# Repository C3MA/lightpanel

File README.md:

# moved to https://www.ccc-mannheim.de/wiki/Lightpanel

# lightpanel v1.0

###Import application note
Do not chain Multiple boards while powering only via USB!

The Voltage converters will reverse feed the second board, and in the process kill most of the LED's on the first board!

ESP32C3 notice:
If flashing while connected to the board, the ESP might damage it's

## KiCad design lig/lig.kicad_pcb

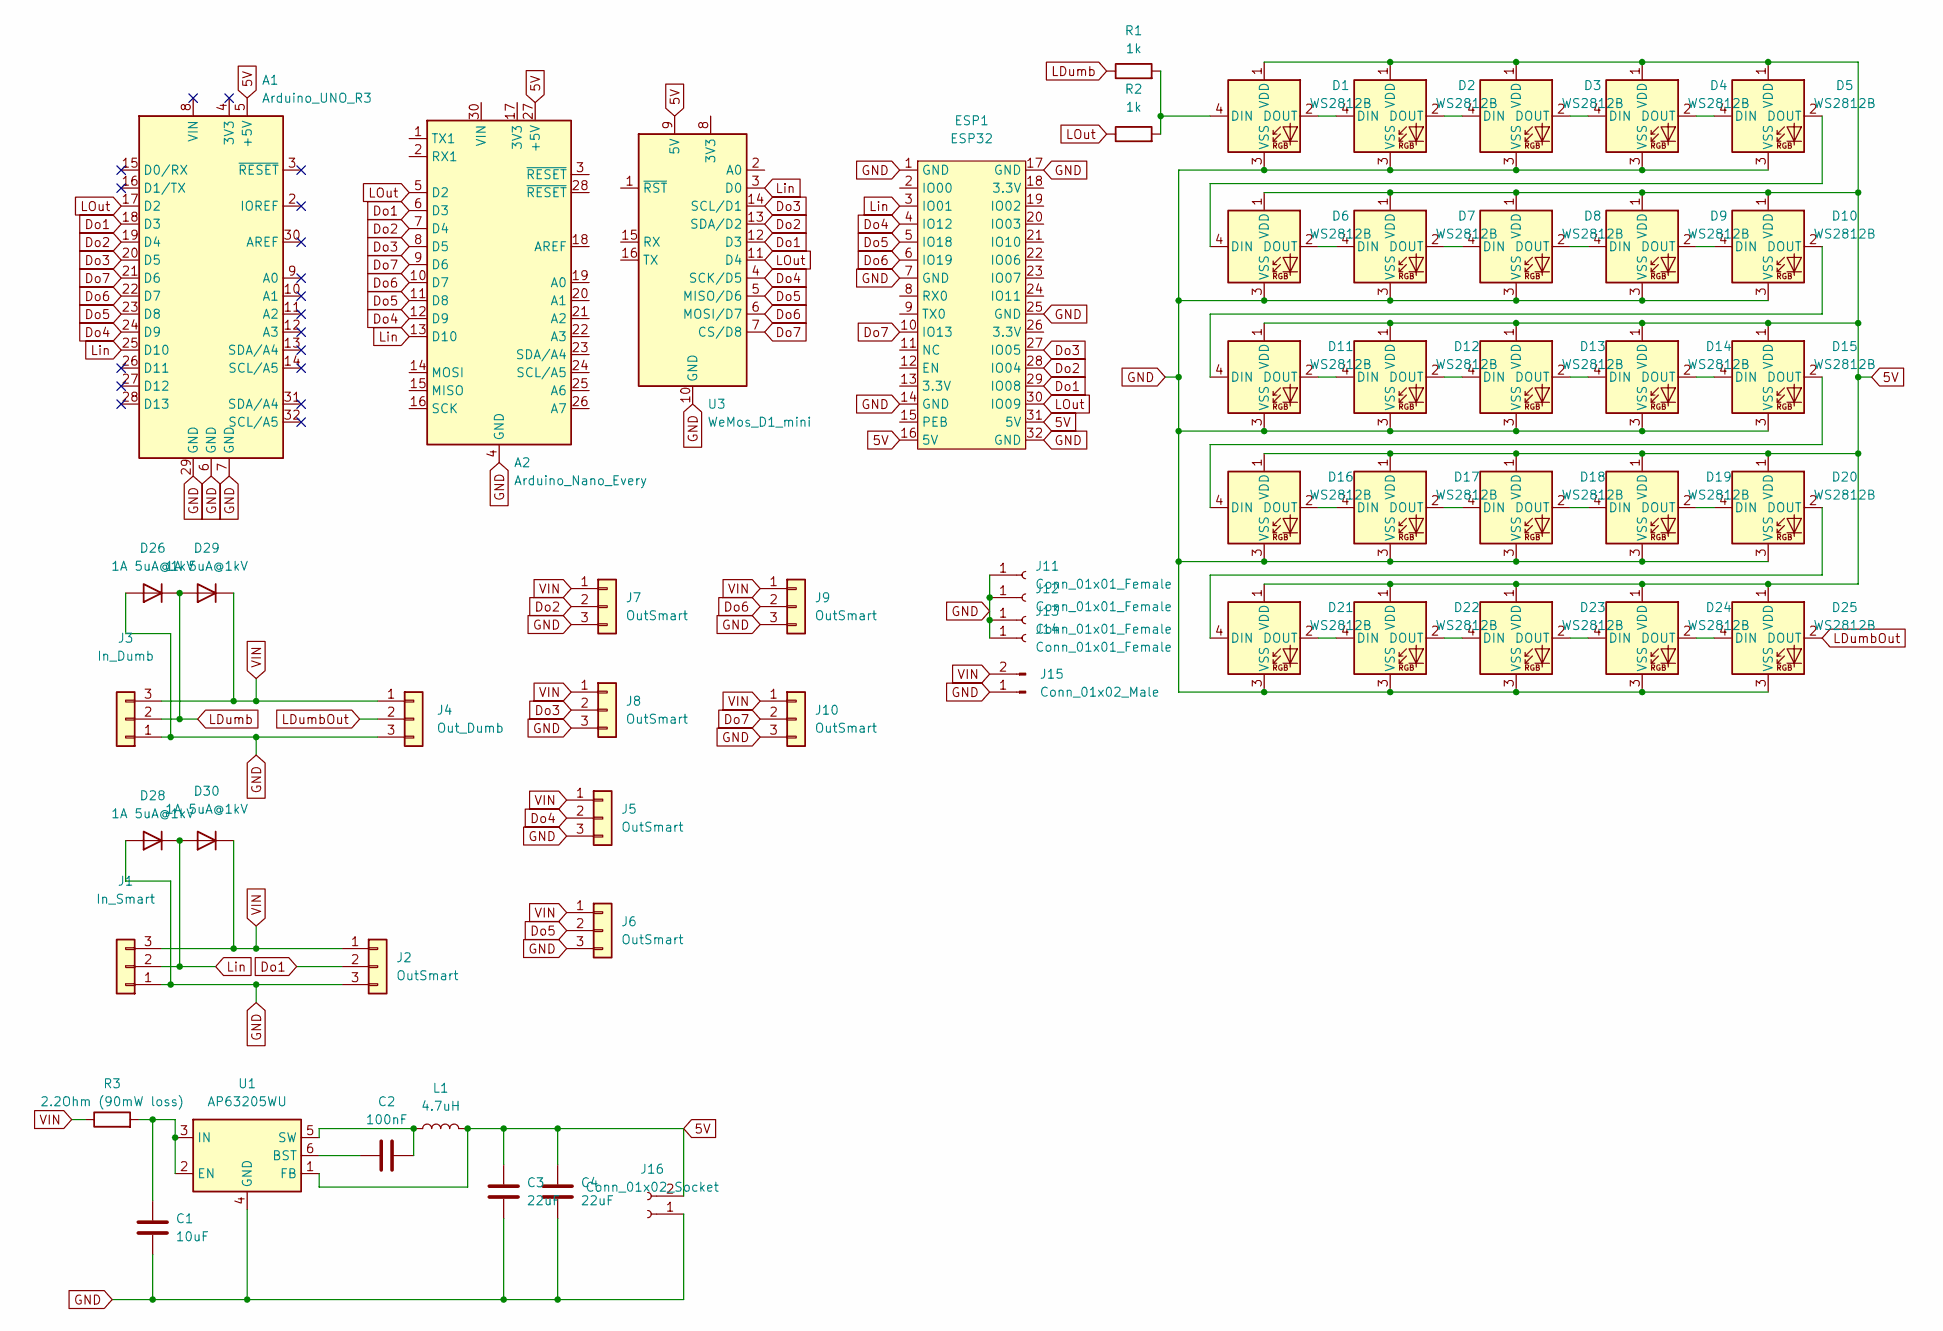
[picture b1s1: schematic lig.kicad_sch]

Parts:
A1: Arduino_UNO_R3
A2: Arduino_Nano_Every; Arduino_Nano
C1: 10uF; C_1206_3216Metric; LCSC C13585
C2: 100nF; C_0603_1608Metric; LCSC C14663
C3, C4: 22uF; C_1206_3216Metric; LCSC C15008
D1, D2, D3, D4, D5, D6, D7, D8, D9, D10, D11, D12, D13, D14, D15, D16, D17, D18, D19, D20, D21, D22, D23, D24, D25: WS2812B; LED_WS2812B_PLCC4_5.0x5.0mm_P3.2mm; LCSC C2843785
D26, D28, D29, D30: 1A 5uA@1kV; D_SOD-123F; LCSC C64898
ESP1: ESP32; Luatos
J1: In_Smart; JST_PH_B3B-PH-SM4-TB_1x03-1MP_P2.00mm_Vertical
J2, J5, J6, J7, J8, J9, J10: OutSmart; JST_PH_B3B-PH-SM4-TB_1x03-1MP_P2.00mm_Vertical
J3: In_Dumb; JST_PH_B3B-PH-SM4-TB_1x03-1MP_P2.00mm_Vertical; LCSC C2688785
J4: Out_Dumb; JST_PH_B3B-PH-SM4-TB_1x03-1MP_P2.00mm_Vertical; LCSC C2688785
J11, J12, J13, J14: Conn_01x01_Female; Solder_Screw_Mount
J15: Conn_01x02_Male; AMASS_XT60-M_1x02_P7.20mm_Vertical
J16: Conn_01x02_Socket; PinHeader_1x02_P2.54mm_Vertical
L1: 4.7uH; L_1210_3225Metric; LCSC C90319
R1, R2: 1k; R_0603_1608Metric; LCSC C21190
R3: 2.2Ohm (90mW loss); R_0805_2012Metric; LCSC C17513
U1: AP63205WU; TSOT-23-6; LCSC C2071056
U3: WeMos_D1_mini; WEMOS_D1_mini_light

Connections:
5V: A1.5 (+5V), A2.27 (+5V), C3.1, C4.1, D1.1 (VDD), D2.1 (VDD), D3.1 (VDD), D4.1 (VDD), D5.1 (VDD), D6.1 (VDD), D7.1 (VDD), D8.1 (VDD), D9.1 (VDD), D10.1 (VDD), D11.1 (VDD), D12.1 (VDD), D13.1 (VDD), D14.1 (VDD), D15.1 (VDD), D16.1 (VDD), D17.1 (VDD), D18.1 (VDD), D19.1 (VDD), D20.1 (VDD), D21.1 (VDD), D22.1 (VDD), D23.1 (VDD), D24.1 (VDD), D25.1 (VDD), ESP1.16 (5V), ESP1.31 (5V), J16.2, L1.2, U1.1 (FB), U3.9 (5V)
Do1: A1.18 (D3), A2.6 (D3), ESP1.29 (IO08), J2.2, U3.12 (D3)
Do2: A1.19 (D4), A2.7 (D4), ESP1.28 (IO04), J7.2, U3.13 (SDA/D2)
Do3: A1.20 (D5), A2.8 (D5), ESP1.27 (IO05), J8.2, U3.14 (SCL/D1)
Do4: A1.24 (D9), A2.12 (D9), ESP1.4 (IO12), J5.2, U3.4 (SCK/D5)
Do5: A1.23 (D8), A2.11 (D8), ESP1.5 (IO18), J6.2, U3.5 (MISO/D6)
Do6: A1.22 (D7), A2.10 (D7), ESP1.6 (IO19), J9.2, U3.6 (MOSI/D7)
Do7: A1.21 (D6), A2.9 (D6), ESP1.10 (IO13), J10.2, U3.7 (CS/D8)
GND: A1.6 (GND), A1.7 (GND), A1.29 (GND), A2.4 (GND), A2.29 (GND), C1.2, C3.2, C4.2, D1.3 (VSS), D2.3 (VSS), D3.3 (VSS), D4.3 (VSS), D5.3 (VSS), D6.3 (VSS), D7.3 (VSS), D8.3 (VSS), D9.3 (VSS), D10.3 (VSS), D11.3 (VSS), D12.3 (VSS), D13.3 (VSS), D14.3 (VSS), D15.3 (VSS), D16.3 (VSS), D17.3 (VSS), D18.3 (VSS), D19.3 (VSS), D20.3 (VSS), D21.3 (VSS), D22.3 (VSS), D23.3 (VSS), D24.3 (VSS), D25.3 (VSS), D26.2 (A), D28.2 (A), ESP1.1 (GND), ESP1.7 (GND), ESP1.14 (GND), ESP1.17 (GND), ESP1.25 (GND), ESP1.32 (GND), J1.1, J2.3, J3.1, J4.3, J5.3, J6.3, J7.3, J8.3, J9.3, J10.3, J11.1, J12.1, J13.1, J14.1, J15.1, J16.1, U1.4 (GND), U3.10 (GND)
LDumb: D26.1 (K), D29.2 (A), J3.2, R1.1
LDumbOut: D25.2 (DOUT), J4.2
LOut: A1.17 (D2), A2.5 (D2), ESP1.30 (IO09), R2.1, U3.11 (D4)
Lin: A1.25 (D10), A2.13 (D10), D28.1 (K), D30.2 (A), ESP1.3 (IO01), J1.2, U3.3 (D0)
unnamed: D1.4 (DIN), R1.2, R2.2
unnamed: D1.2 (DOUT), D2.4 (DIN)
unnamed: D2.2 (DOUT), D3.4 (DIN)
unnamed: D3.2 (DOUT), D4.4 (DIN)
unnamed: D4.2 (DOUT), D5.4 (DIN)
unnamed: D5.2 (DOUT), D6.4 (DIN)
unnamed: D6.2 (DOUT), D7.4 (DIN)
unnamed: D7.2 (DOUT), D8.4 (DIN)
unnamed: D8.2 (DOUT), D9.4 (DIN)
unnamed: D9.2 (DOUT), D10.4 (DIN)
unnamed: D10.2 (DOUT), D11.4 (DIN)
unnamed: D11.2 (DOUT), D12.4 (DIN)
unnamed: D12.2 (DOUT), D13.4 (DIN)
unnamed: D13.2 (DOUT), D14.4 (DIN)
unnamed: D14.2 (DOUT), D15.4 (DIN)
unnamed: D15.2 (DOUT), D16.4 (DIN)
unnamed: D16.2 (DOUT), D17.4 (DIN)
unnamed: D17.2 (DOUT), D18.4 (DIN)
unnamed: D18.2 (DOUT), D19.4 (DIN)
unnamed: D19.2 (DOUT), D20.4 (DIN)
unnamed: D20.2 (DOUT), D21.4 (DIN)
unnamed: D21.2 (DOUT), D22.4 (DIN)
unnamed: D22.2 (DOUT), D23.4 (DIN)
unnamed: D23.2 (DOUT), D24.4 (DIN)
unnamed: D24.2 (DOUT), D25.4 (DIN)
unnamed: C2.1, U1.6 (BST)
unnamed: C1.1, R3.2, U1.2 (EN), U1.3 (IN)
unnamed: C2.2, L1.1, U1.5 (SW)
VIN: D29.1 (K), D30.1 (K), J1.3, J2.1, J3.3, J4.1, J5.1, J6.1, J7.1, J8.1, J9.1, J10.1, J15.2, R3.1

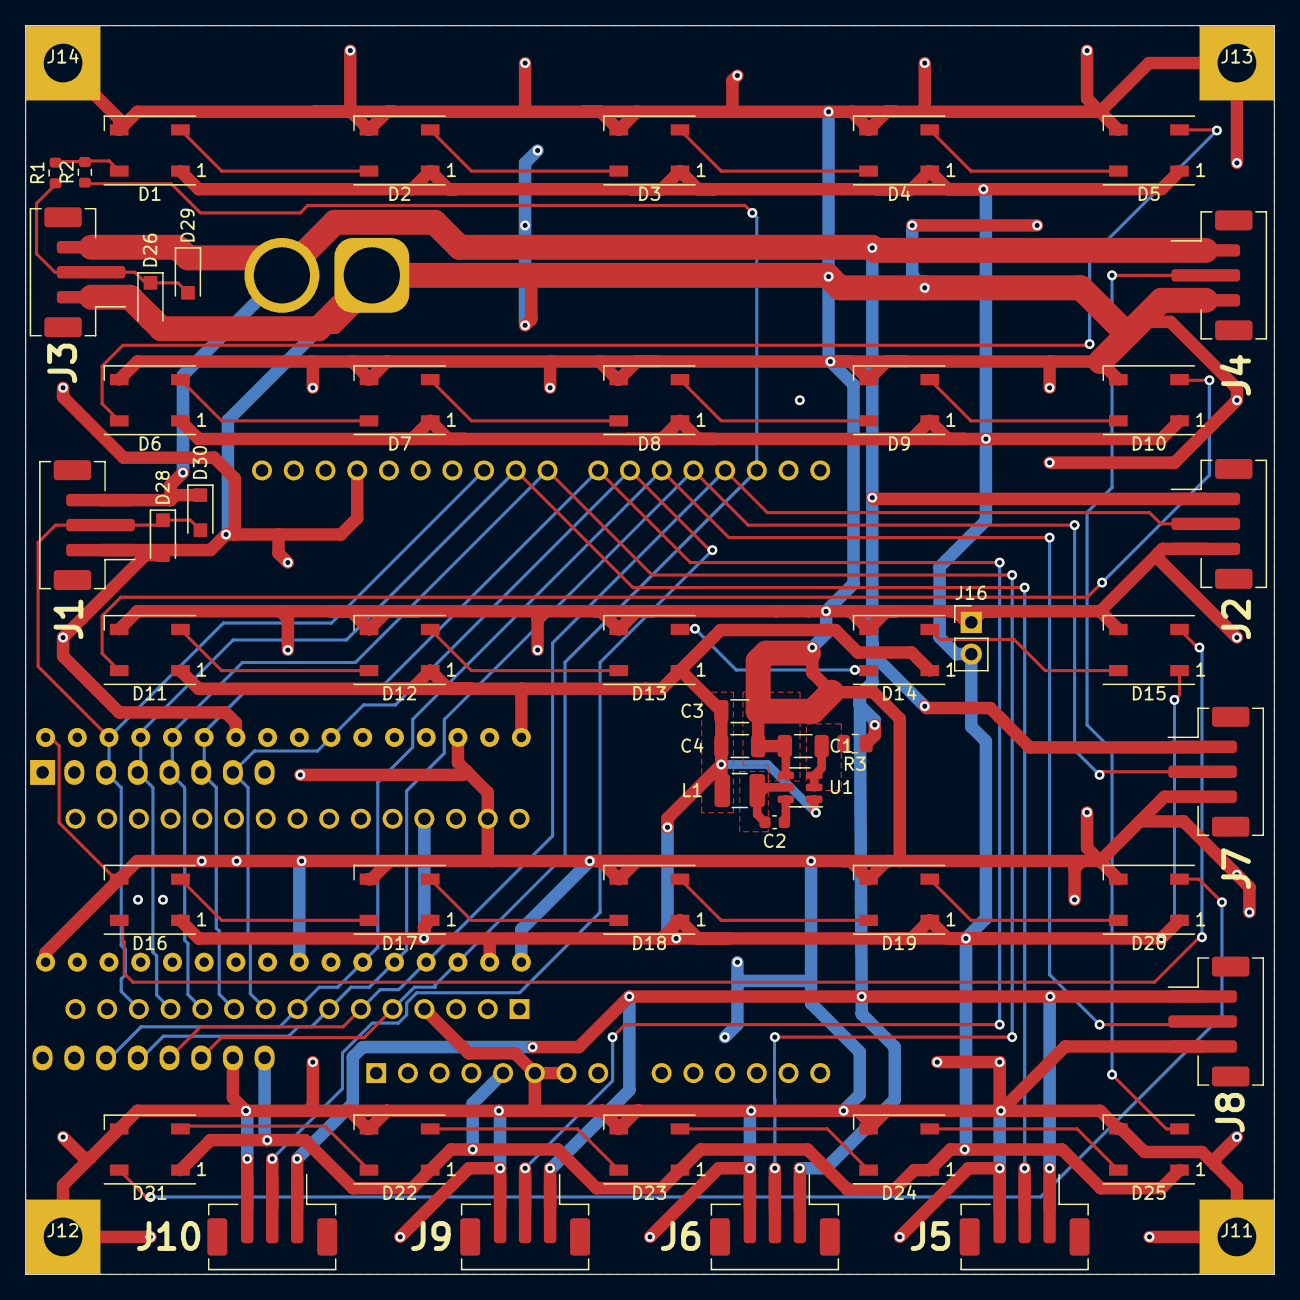
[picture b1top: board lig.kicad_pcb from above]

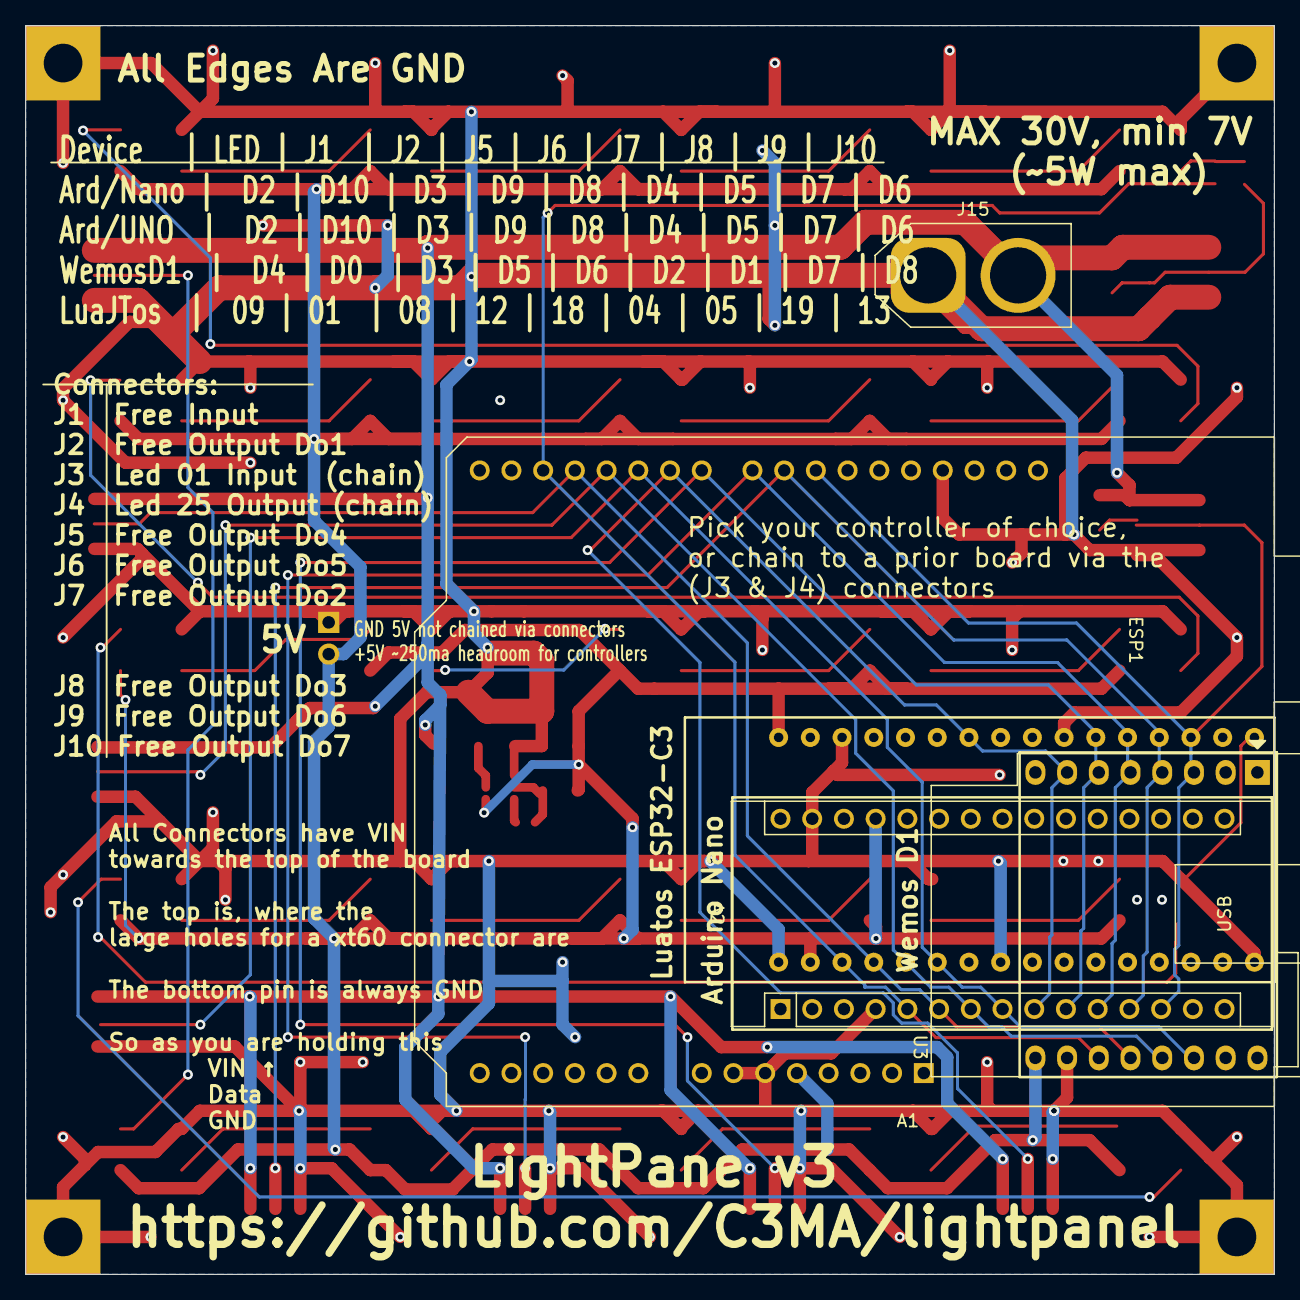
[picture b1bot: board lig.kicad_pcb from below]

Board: 2 copper layers, 100.0 x 100.0 mm, 58 parts (5 on the bottom side), 42 nets.

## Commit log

2023-03-23 initial data
2023-05-28 added footprint
2023-06-30 added important application note
2023-12-27 v2 changes
2023-12-27 für ollo
2024-02-22 v2 diodes and simplification
